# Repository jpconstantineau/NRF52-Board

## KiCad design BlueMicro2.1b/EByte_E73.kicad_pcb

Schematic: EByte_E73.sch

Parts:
C1: 1uF; C_0402_1005Metric; LCSC C52923
C2, C9, C10, C11, C12: 100nF; C_0402_1005Metric; LCSC C1525
C3, C5, C7, C8: 10uF; C_0402_1005Metric; LCSC C15525
C4: 100 pF; C_0402_1005Metric; LCSC C1546
C6: 1nF; C_0402_1005Metric; LCSC C1523
D1: B5819W; D_SOD-123; LCSC C8598
D2, D3: D; D_SOD-123; LCSC C81598
D4: BLUE; LED_0603_1608Metric; LCSC C72041
D5, D6: RED; LED_0603_1608Metric; LCSC C2286
J1: USB_OTG; USB_Micro-B_Molex-105017-0001
J2: Serial Connector; Pin_Header_Straight_2x03_Pitch2.54mm
J3: Conn_01x02; Pin_Header_Straight_1x02_Pitch2.54mm
L1: 10uH; L_0805_2012Metric; LCSC C1046
Q1: SI2301CDS-T1-GE3; SOT-23; LCSC C10487
R1: 10k; R_0402_1005Metric; LCSC C25744
R2: 100K; R_0402_1005Metric; LCSC C25741
R3: 10K; R_0402_1005Metric; LCSC C25744
R4: 806K; R_0603_1608Metric; LCSC C23250
R5: 2M; R_0603_1608Metric; LCSC C22976
R6, R8, R9, R10: 1k; R_0402_1005Metric; LCSC C11702
R7: JUMP; R_0402_1005Metric; LCSC C17168
U1: E73-2G4M04S
U2: ProMicro; Pro_Micro
U3: AP2112K-3.3; SOT-23-5; LCSC C51118
U4: CH340C; SO-16-N; LCSC C84681
U6: TP4054ST; SOT-23-5; LCSC C32574

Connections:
/DTR: C9.2, U4.13
/Data+: J1.3, U4.5
/Data-: J1.2, U4.6
/LED1: R9.1, U1.32
/LED2: R8.1, U1.34
/P0.02: U1.17, U2.8
/P0.03: U1.18, U2.7
/P0.04: U1.19, U2.6
/P0.05: U1.20, U2.5
/P0.07: U1.22, U2.14
/P0.11: U1.26, U2.12
/P0.15: U1.30, U2.23
/P0.16: U1.31, U2.24
/P0.27: U1.7, U2.19
/P0.28: U1.8, U2.20
/P0.29: U1.9, U2.21
/P0.30: U1.10, U2.22
/P0.31: C6.1, R4.2, R5.1, U1.11
/VBatt: C7.1, J3.1, Q1.3, R4.1, R7.1, U6.3
/VBus: C8.1, C11.1, D1.2 (A), D2.2, J1.1, Q1.1, R2.1, R10.2, U6.4
GND: C1.2, C2.2, C3.2, C4.2, C5.2, C6.2, C7.2, C8.2, C10.2, C11.2, C12.2, D4.1, D5.1, J1.5, J2.4, J3.2, R2.2, R3.2, R5.2, U1.0, U1.1, U1.2, U1.15, U1.42, U1.43, U2.2, U2.15, U2.16, U3.2, U4.1, U6.2
MISO: U1.29, U2.10
MOSI: U1.28, U2.11
unnamed: C1.1, L1.1, U1.12
unnamed: C2.1, U1.14
unnamed: C4.1, U1.4
unnamed: C5.1, D1.1 (K), Q1.2, U3.1, U3.3
unnamed: C10.1, U4.4
unnamed: C12.1, D3.1, U4.16
unnamed: D2.1, D3.2
unnamed: D4.2, R8.2
unnamed: D5.2, R9.2
unnamed: D6.1, U6.1
unnamed: D6.2, R10.1
unnamed: L1.2, U1.13
unnamed: R3.1, U6.5
unnamed: R6.2, U4.2
unnamed: R7.2, U2.1
RESET: C9.1, R1.1, U1.36, U2.3
RXD: J2.1, R6.1, U1.23
SCK: U1.27, U2.9
SCL: U1.6, U2.18
SDA: U1.5, U2.17
SWDCLK: J2.5, U1.37
SWDIO: J2.6, U1.38
SWO: U1.33, U2.13
TXD: J2.2, U1.21, U4.3
VCC: C3.1, J2.3, R1.2, U1.16, U2.4, U3.5

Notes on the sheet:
RESET AND USB RESET
Joint Serial/SWD Header
Power and Filtering
LiPo Charging

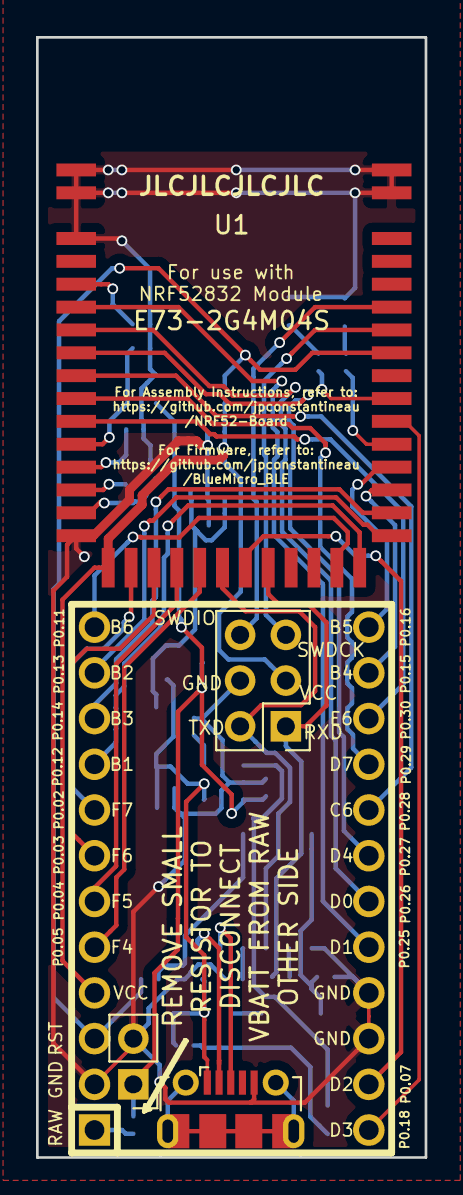
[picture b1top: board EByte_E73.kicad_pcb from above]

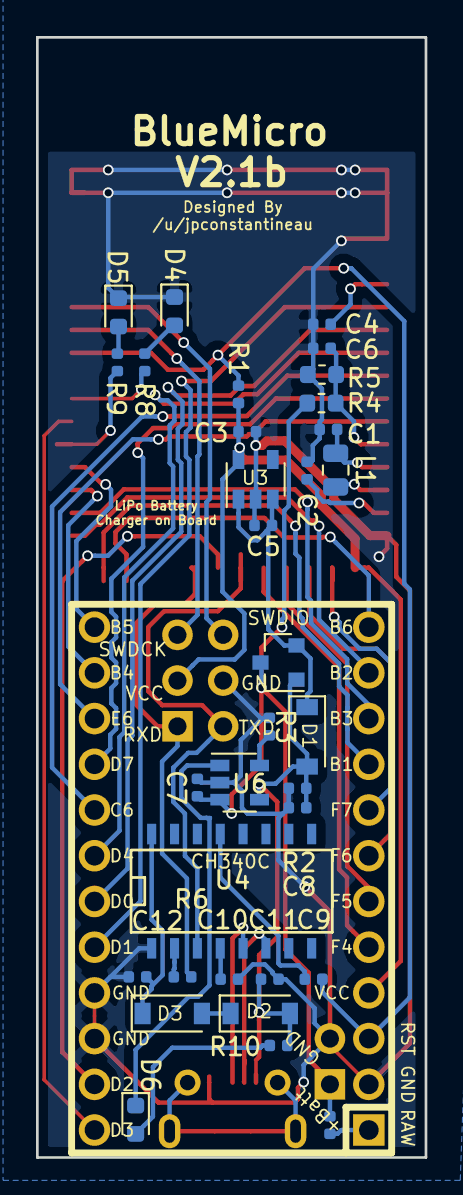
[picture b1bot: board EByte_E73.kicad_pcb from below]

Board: 2 copper layers, 21.6 x 62.2 mm, 38 parts (34 on the bottom side), 48 nets.

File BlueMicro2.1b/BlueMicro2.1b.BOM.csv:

Comment,Designator,Footprint,LCSC, LCSC
"1uF","C1","Capacitor_SMD:C_0402_1005Metric","","C52923"
"100nF","C2,C9,C10,C11,C12","Capacitor_SMD:C_0402_1005Metric","","C1525"
"10uF","C3,C5,C7,C8","Capacitor_SMD:C_0402_1005Metric","","C15525"
"100 pF","C4","Capacitor_SMD:C_0402_1005Metric","","C1546"
"1nF","C6","Capacitor_SMD:C_0402_1005Metric","","C1523"
"MBR120","D1","Diode_SMD:D_SOD-123","","C130880"
"D","D2,D3","Diode_SMD:D_SOD-123","","C81598"
"BLUE","D4","LED_SMD:LED_0603_1608Metric","","C72041"
"RED","D5,D6","LED_SMD:LED_0603_1608Metric","","C2286"
"USB_OTG","J1","Connectors_USB:USB_Micro-B_Molex-105017-0001",""
"Serial Connector","J2","Pin_Headers:Pin_Header_Straight_2x03_Pitch2.54mm",""
"Conn_01x02","J3","Pin_Headers:Pin_Header_Straight_1x02_Pitch2.54mm",""
"10uH","L1","Inductor_SMD:L_0805_2012Metric","","C1046"
"SI2301CDS-T1-GE3","Q1","TO_SOT_Packages_SMD:SOT-23","","C10487"
"10k","R1","Resistor_SMD:R_0402_1005Metric","","C25744"
"100K","R2","Resistor_SMD:R_0402_1005Metric","","C25741"
"10K","R3","Resistor_SMD:R_0402_1005Metric","","C25744"
"806K","R4","Resistor_SMD:R_0603_1608Metric","","C23250"
"2M","R5","Resistor_SMD:R_0603_1608Metric","","C22976"
"1k","R6,R8,R9,R10","Resistor_SMD:R_0402_1005Metric","","C11702"
"JUMP","R7","Resistor_SMD:R_0402_1005Metric","","C17168"
"E73-2G4M04S","U1","E73:E73-2G4M04S",""
"ProMicro","U2","footprints:Pro_Micro",""
"AP2112K-3.3","U3","Package_TO_SOT_SMD:SOT-23-5","","C51118"
"CH340C","U4","SMD_Packages:SO-16-N","","C84681"
"TP4054ST","U6","Package_TO_SOT_SMD:SOT-23-5","","C32574"

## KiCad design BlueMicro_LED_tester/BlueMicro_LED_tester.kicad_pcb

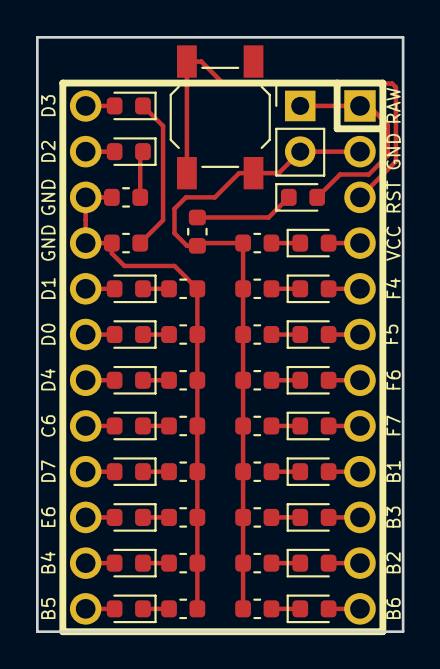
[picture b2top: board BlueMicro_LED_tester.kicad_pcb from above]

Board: 2 copper layers, 20.3 x 33.0 mm, 43 parts (1 on the bottom side), 43 nets.

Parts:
D1, D2, D3, D4, D5, D6, D7, D8, D9, D10, D11, D12, D13, D14, D15, D16, D17, D18, D19, D20: LED; LED_0603_1608Metric
J1: Conn_01x02_Male; PinHeader_1x02_P2.54mm_Vertical
R1, R2, R3, R4, R5, R6, R7, R8, R9, R10, R11, R12, R13, R14, R15, R16, R17, R18, R19, R20: 2k2; R_0603_1608Metric
SW1: SW_PUSH; SW_TACT_ALPS_SKQGABE010
U1: ProMicro; Pro_Micro

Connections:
unnamed: D1.1, R1.1
unnamed: D1.2, J1.1, U1.1
unnamed: D2.1, R2.1
unnamed: D2.2, U1.13
unnamed: D3.1, R3.1
unnamed: D3.2, U1.14
unnamed: D4.1, R4.1
unnamed: D4.2, U1.17
unnamed: D5.1, R5.1
unnamed: D5.2, U1.18
unnamed: D6.1, R6.1
unnamed: D6.2, U1.19
unnamed: D7.1, R7.1
unnamed: D7.2, U1.20
unnamed: D8.1, R8.1
unnamed: D8.2, U1.21
unnamed: D9.1, R9.1
unnamed: D9.2, U1.22
unnamed: D10.1, R10.1
unnamed: D10.2, U1.23
unnamed: D11.1, R11.1
unnamed: D11.2, U1.24
unnamed: D12.1, R12.1
unnamed: D12.2, U1.4
unnamed: D13.1, R13.1
unnamed: D13.2, U1.5
unnamed: D14.1, R14.1
unnamed: D14.2, U1.6
unnamed: D15.1, R15.1
unnamed: D15.2, U1.7
unnamed: D16.1, R16.1
unnamed: D16.2, U1.8
unnamed: D17.1, R17.1
unnamed: D17.2, U1.9
unnamed: D18.1, R18.1
unnamed: D18.2, U1.10
unnamed: D19.1, R19.1
unnamed: D19.2, U1.11
unnamed: D20.1, R20.1
unnamed: D20.2, U1.12
unnamed: J1.2, R1.2, R12.2, R13.2, R14.2, R15.2, R16.2, R17.2, R18.2, R19.2, R20.2, SW1.2, U1.2
unnamed: R2.2, R3.2, R4.2, R5.2, R6.2, R7.2, R8.2, R9.2, R10.2, R11.2, U1.15, U1.16
unnamed: SW1.1, U1.3

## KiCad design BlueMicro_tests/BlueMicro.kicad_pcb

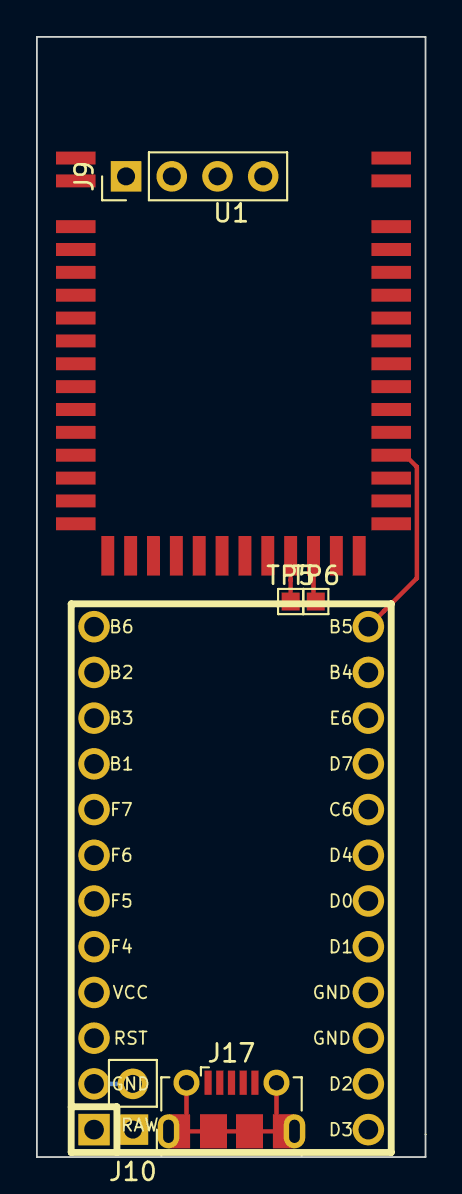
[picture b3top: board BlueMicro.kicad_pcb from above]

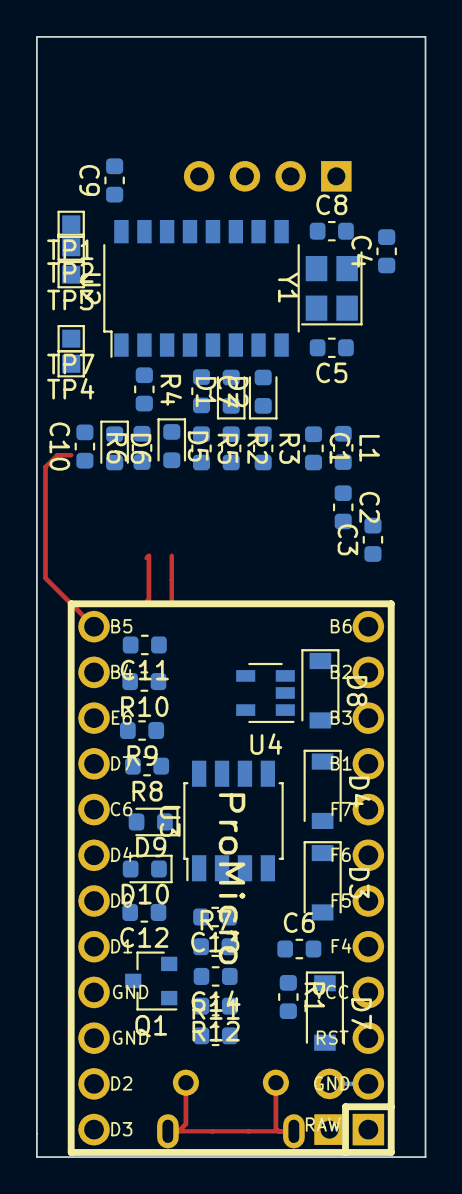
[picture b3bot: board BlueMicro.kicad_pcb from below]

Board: 2 copper layers, 21.6 x 62.2 mm, 54 parts (48 on the bottom side), 59 nets.

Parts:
C1: 1uF; C_0603_1608Metric
C2, C10: 0.1uF; C_0603_1608Metric
C3, C11, C12, C13: 10uF; C_0603_1608Metric
C4: 100pF; C_0603_1608Metric
C5, C8: 22pF; C_0603_1608Metric
C6, C7, C9: 100nF; C_0603_1608Metric
C14: 1nF; C_0603_1608Metric
D1: BLUE; LED_0603_1608Metric
D2, D5, D6, D10: RED; LED_0603_1608Metric
D3, D4, D7: 1N4148W; D_SOD-123
D8: B5819W; D_SOD-123
D9: GREEN; LED_0603_1608Metric
J9: Conn_01x04; PinHeader_1x04_P2.54mm_Vertical
J10: Conn_01x02; PinHeader_1x02_P2.54mm_Vertical
J17: USB_B_Micro; USB_Micro-B_Molex-105017-0001
L1: 10uH; L_0603_1608Metric
Q1: Si2301CDS; SOT-23
R1, R7, R9: 10k; R_0603_1608Metric
R2, R3, R4, R5, R6, R10: 1k; R_0603_1608Metric
R8: 100k; R_0603_1608Metric
R11: 806k; R_0603_1608Metric
R12: 2M; R_0603_1608Metric
TP1, TP2, TP3, TP4, TP5, TP6, TP7: TestPoint_Probe; TestPoint_Pad_1.0x1.0mm
U1: E73-2G4M04S
U2: CH340G; SOP-16_4.4x10.4mm_P1.27mm
U3: TP4056; SSOP-8_3.95x5.21x3.27mm_P1.27mm
U4: AP2112K-3.3; SOT-23-5
U5: ProMicro; Pro_Micro
Y1: 12MHz; Crystal_SMD_3225-4Pin_3.2x2.5mm

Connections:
B1: U1.27, U5.9
B2: U1.28, U5.11
B3: U1.29, U5.10
B4: U1.30, U5.23
B5: U1.31, U5.24
B6: U1.26, U5.12
BLUELED: D1.2, U1.34
C6: U1.8, U5.20
D0: U1.6, U5.18
D1: U1.5, U5.17
D2: U1.22, U5.14
D3: U1.33, U5.13
D4: U1.7, U5.19
D7: U1.9, U5.21
DFU: TP4.1, U1.35
DTR: C10.2, U2.13
E6: U1.10, U5.22
F4: U1.20, U5.5
F5: U1.19, U5.6
F6: U1.18, U5.7
F7: U1.17, U5.8
FACTORYRESET: TP3.1, U1.39
GND: C1.2, C2.2, C3.2, C4.2, C5.2, C6.2, C7.2, C8.2, C9.2, C11.2, C12.2, C13.2, C14.2, J9.2, J10.2, J17.5, R2.2, R3.2, R7.1, R8.1, R12.2, U1.0, U1.1, U1.2, U1.15, U1.42, U1.43, U2.1, U3.1, U3.3, U4.2, U5.2, U5.15, U5.16, Y1.2, Y1.4
NFC1: TP5.1, U1.24
NFC2: TP6.1, U1.25
unnamed: C1.1, L1.1, U1.12
unnamed: C2.1, U1.14
unnamed: C4.1, U1.4
unnamed: C5.1, U2.7, Y1.1
unnamed: C7.1, U2.4
unnamed: C8.1, U2.8, Y1.3
unnamed: C9.1, D4.1, R5.2, R6.1, U2.16
unnamed: C12.1, D8.1, Q1.2, U4.1, U4.3
unnamed: C14.1, R11.2, R12.1, U1.11
unnamed: D1.1, R2.1
unnamed: D2.1, R3.1
unnamed: D3.1, D4.2
unnamed: D5.2, R5.1
unnamed: D6.2, R6.2
unnamed: D9.1, U3.6
unnamed: D9.2, R9.2
unnamed: D10.1, U3.7
unnamed: D10.2, R10.2
unnamed: J17.2, U2.6
unnamed: J17.3, U2.5
unnamed: L1.2, U1.13
unnamed: R4.1, U2.2
unnamed: R7.2, U3.2
P0.23: TP2.1, U1.40
P0.24: TP1.1, U1.41
REDLED: D2.2, U1.32
RESET: C10.1, D7.2, R1.2, TP7.1, U1.36, U5.3
RXD: D6.1, R4.2, U1.23
SWDCLK: J9.3, U1.37
SWDIO: J9.4, U1.38
TXD: D5.1, U1.21, U2.3
VBATT: C13.1, J10.1, Q1.3, R11.1, U3.5
VBUS: C6.1, C11.1, D3.2, D8.2, J17.1, Q1.1, R8.2, R9.1, R10.1, U3.4, U3.8
VCC: C3.1, D7.1, J9.1, R1.1, U1.16, U4.5, U5.4

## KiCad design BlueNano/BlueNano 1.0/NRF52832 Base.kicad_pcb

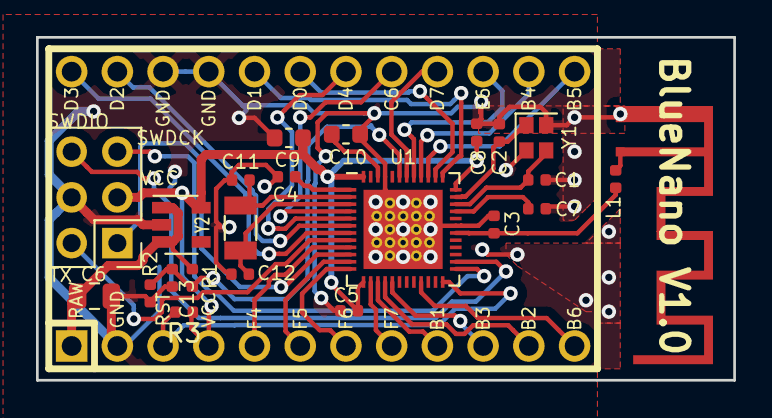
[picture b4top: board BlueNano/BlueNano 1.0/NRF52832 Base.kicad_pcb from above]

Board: 2 copper layers, 38.7 x 19.0 mm, 24 parts (0 on the bottom side), 36 nets.

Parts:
AE1: Antenna_Shield; ti-an043-antenna
C1, C2, C11, C12: 12pF; C_0402_1005Metric
C3: 0.8pF; C_0402_1005Metric
C4, C5, C8: 100nF; C_0402_1005Metric
C6: 10uF; C_0805_2012Metric
C7: 100pF; C_0402_1005Metric
C9: 4.7uF; C_0603_1608Metric
C10: 1uF; C_0603_1608Metric
C13: 1nF; C_0402_1005Metric
J1: Conn_01x06; PinHeader_2x03_P2.54mm_Vertical
L1: 3.9nH; L_0402_1005Metric
R1: 806k; R_0402_1005Metric
R2: 2M; R_0402_1005Metric
R3: 10k; R_0402_1005Metric
U1: NRF52832-QFAA-R; QFN-48-1EP_6x6mm_P0.4mm_EP4.66x4.66mm_ThermalVias
U2: ProMicro; Pro_Micro
U3: AP2112K-3.3; SOT-23-5
Y1: 32MHz; Crystal_SMD_2016-4Pin_2.0x1.6mm
Y2: 32.768kHz; Crystal_SMD_3215-2Pin_3.2x1.5mm

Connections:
/P0.02: U1.4, U2.20
/P0.03: U1.5, U2.19
/P0.04: U1.6, U2.14
/P0.05: U1.7, U2.13
/P0.07: U1.9, U2.5
/P0.09: U1.11, U2.6
/P0.10: U1.12, U2.7
/P0.11: U1.14, U2.8
/P0.18: U1.21, U2.12
/P0.27: U1.39, U2.24
/P0.28: U1.40, U2.23
/P0.29: U1.41, U2.22
/P0.30: U1.42, U2.21
GND: AE1.2, C1.1, C2.1, C3.2, C4.2, C5.2, C6.2, C7.1, C8.2, C9.2, C10.2, C11.2, C12.2, C13.2, J1.4, R2.2, U1.31, U1.45, U1.49, U2.2, U2.15, U2.16, U3.2, Y1.2, Y1.4
MISO: U1.17, U2.10
MOSI: U1.16, U2.11
unnamed: AE1.1, L1.2
unnamed: C1.2, U1.34, Y1.3
unnamed: C2.2, U1.35, Y1.1
unnamed: C3.1, L1.1, U1.30
unnamed: C4.1, U1.1
unnamed: C7.2, U1.33
unnamed: C10.1, U1.46
unnamed: C11.1, U1.2, Y2.1
unnamed: C12.1, U1.3, Y2.2
RAW: C6.1, R1.1, U2.1, U3.1, U3.3
RESET: R3.2, U1.24, U2.3
RXD: J1.1, U1.10
SCK: U1.15, U2.9
SCL: U1.38, U2.18
SDA: U1.37, U2.17
SWDCLK: J1.5, U1.25
SWDIO: J1.6, U1.26
TXD: J1.2, U1.8
VBATT: C13.1, R1.2, R2.1, U1.43
VCC: C5.1, C8.1, C9.1, J1.3, R3.1, U1.13, U1.36, U1.48, U2.4, U3.5

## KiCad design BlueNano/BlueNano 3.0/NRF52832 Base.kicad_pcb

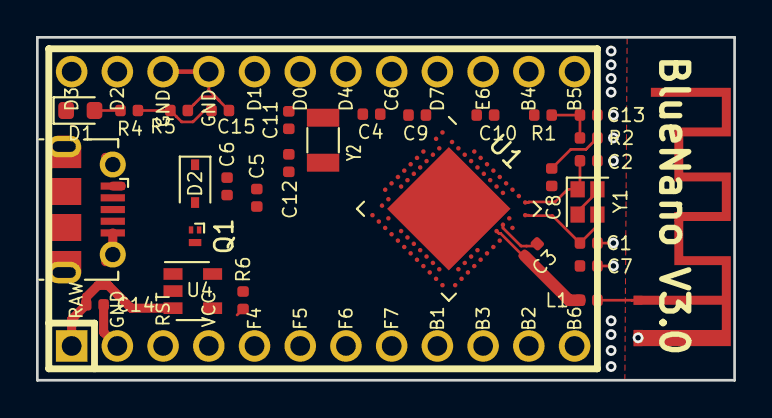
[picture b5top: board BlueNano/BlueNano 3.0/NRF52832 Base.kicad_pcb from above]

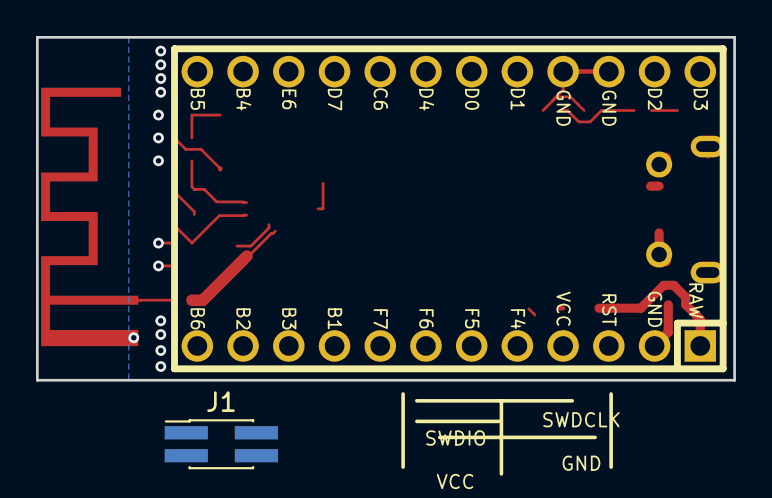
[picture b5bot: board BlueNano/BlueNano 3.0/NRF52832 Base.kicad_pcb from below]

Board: 2 copper layers, 38.7 x 19.0 mm, 32 parts (2 on the bottom side), 21 nets.

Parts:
AE1: Antenna_Shield; ti-an043-antenna-flipped
C1, C2, C11, C12: 12pF; C_0402_1005Metric
C3: 0.8pF; C_0402_1005Metric
C4, C5, C8: 100nF; C_0402_1005Metric
C6, C14, C15: 10uF; C_0402_1005Metric
C7: 100pF; C_0402_1005Metric
C9: 4.7uF; C_0402_1005Metric
C10: 1uF; C_0402_1005Metric
C13: 1nF; C_0402_1005Metric
D1: LED; LED_0603_1608Metric
D2: B140WS-7; D_SOD-323
J1: Conn_01x06; PinHeader_2x02_P1.27mm_Vertical_SMD
J2: USB_B_Micro; USB_Micro-B_Molex-105017-0001
L1: 3.9nH; L_0402_1005Metric
Q1: LP0404N3T5G; Diodes_DFN1006-3
R1: 806k; R_0402_1005Metric
R2: 2M; R_0402_1005Metric
R4: 330; R_0402_1005Metric
R5: 100k; R_0402_1005Metric
R6: 10k; R_0402_1005Metric
U1: nRF52840; Nordic_AQFN-73-1EP_7x7mm_P0.5mm
U2: ProMicro; Pro_Micro
U4: TP4054ST; SOT-23-5
Y1: 32MHz; Crystal_SMD_2016-4Pin_2.0x1.6mm
Y2: 32.768kHz; Crystal_SMD_3215-2Pin_3.2x1.5mm

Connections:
/D+: J2.3, U1.AD6
/D-: J2.2, U1.AD4
/VBus: C15.1, D2.2, J2.1, Q1.1, R4.1, R5.1, U4.4
GND: AE1.2, C1.1, C2.1, C3.2, C4.2, C5.2, C6.2, C7.1, C8.2, C9.2, C10.2, C11.1, C12.1, C13.2, C14.2, C15.2, J1.4, J2.5, J2.6, R2.2, R5.2, R6.2, U1.B7, U1.EP, U1.F23, U2.2, U2.15, U2.16, U4.2, Y1.2, Y1.4
unnamed: AE1.1, L1.1
unnamed: C1.2, U1.B24, Y1.3
unnamed: C2.2, U1.A23, Y1.1
unnamed: C3.1, L1.2, U1.H23
unnamed: C6.1, D2.1, Q1.2
unnamed: C11.2, U1.D2, Y2.1
unnamed: C12.2, U1.F2, Y2.2
unnamed: D1.1, U4.1
unnamed: D1.2, R4.2
unnamed: R6.1, U4.5
unnamed: U1.A22, U1.AD14, U1.AD23, U1.B1, U1.W1
RAW: C14.1, Q1.3, R1.1, U2.1, U4.3
RESET: U1.AC13, U2.3
SWDCLK: J1.2, U1.AA24
SWDIO: J1.1, U1.AC24
VBATT: C13.1, R1.2, R2.1
VCC: C9.1, J1.3, U2.4

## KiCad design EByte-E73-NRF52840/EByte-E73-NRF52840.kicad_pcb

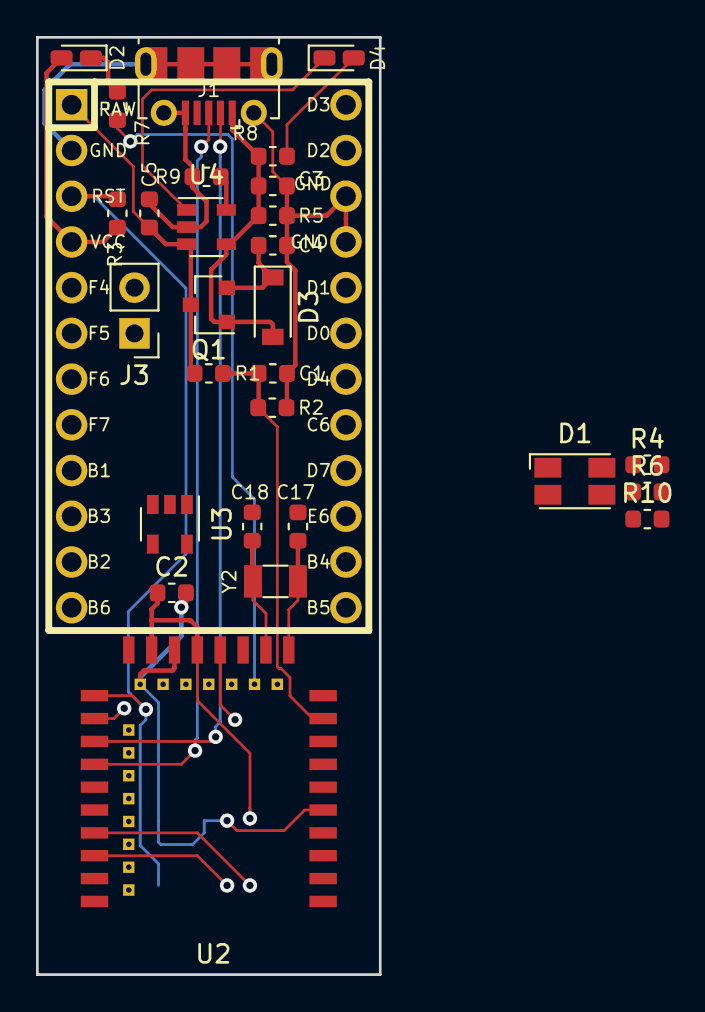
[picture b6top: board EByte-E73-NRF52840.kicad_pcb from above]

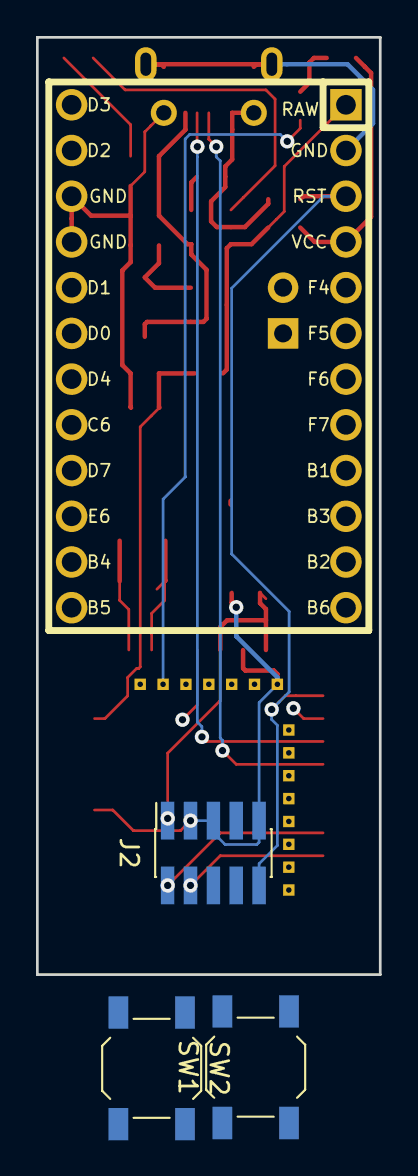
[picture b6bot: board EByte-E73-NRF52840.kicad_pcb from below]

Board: 2 copper layers, 19.1 x 52.1 mm, 32 parts (3 on the bottom side), 26 nets.

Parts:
C1: 1nF; C_0603_1608Metric
C2, C3, C4, C5: 10uF; C_0603_1608Metric
C17, C18: 12pF; C_0603_1608Metric
D1: HQ17-2303BGRC; LED_Avago_PLCC4_3.2x2.8mm_CW
D2, D4: LED; LED_0603_1608Metric_Castellated
D3: D_Schottky; D_SOD-123
J1: USB_B_Micro; USB_Micro-B_Molex-105017-0001
J2: SWD Header; PinSocket_2x05_P1.27mm_Vertical_SMD
J3: Conn_01x02; PinHeader_1x02_P2.54mm_Vertical
Q1: TP0610T; SOT-23
R1: 806k; R_0603_1608Metric
R2: 2M; R_0603_1608Metric
R3, R9: 10k; R_0603_1608Metric
R4: 1k2; R_0603_1608Metric
R5: 100k; R_0603_1608Metric
R6: 2k2; R_0603_1608Metric
R7, R8: 330; R_0603_1608Metric
R10: 330R; R_0603_1608Metric
SW1: DFU; SW_TACT_ALPS_SKQGABE010
SW2: FRST; SW_TACT_ALPS_SKQGABE010
U1: ProMicro; Pro_Micro
U2: E73-2G4M08S1C; 2G4M08S1C
U3: AP2112K-3.3; SOT-23-5
U4: TP4054ST; SOT-23-5
Y2: 32.768kHz; Crystal_SMD_3215-2Pin_3.2x1.5mm

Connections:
/D+: J1.3, U2.31
/D-: J1.2, U2.29
/LED1: R7.2, U2.14
/LED2B: R10.2, U2.20
/LED2G: R6.2, U2.17
/LED2R: R4.2, U2.16
/P0.31: C1.1, R1.2, R2.1, U2.9
/P1.10: SW2.2, U2.2
/RESET: J2.10, R3.2, U1.3, U2.26
/SW1: SW1.2, U2.42
/SWDCLK: J2.4, U2.39
/SWDIO: J2.2, U2.37
/VBatt: C5.1, J3.1, Q1.3, R1.1, U1.1, U4.3
/VBus: C3.1, D3.2, J1.1, Q1.1, R5.1, R8.2, U2.27, U4.4
GND: C1.2, C2.2, C3.2, C4.2, C5.2, C17.2, C18.2, J1.5, J1.6, J2.3, J2.5, J2.9, J3.2, R2.2, R5.2, R9.2, SW1.1, SW2.1, U1.2, U1.15, U1.16, U2.5, U2.21, U2.24, U3.2, U4.2
unnamed: C4.1, D3.1, Q1.2, U3.1, U3.3
unnamed: C17.1, U2.11, Y2.1
unnamed: C18.1, U2.13, Y2.2
unnamed: D1.1, R4.1
unnamed: D1.2, R6.1
unnamed: D1.3, R10.1
unnamed: D2.1, R7.1
unnamed: D4.1, U4.1
unnamed: D4.2, R8.1
unnamed: R9.1, U4.5
VDD: C2.1, D1.4, D2.2, J2.1, R3.1, U1.4, U2.19, U2.23, U3.5
